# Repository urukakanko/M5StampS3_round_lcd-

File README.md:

# M5StampS3ラウンド液晶モジュール

写真左：M5StampS3実装済　　　　写真右：M5StampS3未実装

M5StampS3を使用して1.28インチ240ｘ240ドットの円形液晶を駆動する基板モジュールです。

円形液晶の裏にM5StampS3を配置することで、とても小さくスリムな形状になりました。

円形液晶にはGC9A01というコントローラーが使用されていますが、対応したグラフィックライブラリが数種類公開されています。

本モジュールは「グラフィックライブラリの使い方を理解して液晶モジュールを駆動出来る人」をターゲットにしております。

# 2026年10月販売分よりM5StampS3実装品はM5StampS3Aを実装しています

# 2023年5月5日までにM5StampS3実装品を購入された方へのお詫び

裏面のMacAddressがプリントされたラベルと実際のMacAddressが異なっている可能性があります。

MacAddress情報が必要な場合は以下サンプルソースで画面表示する様にしましたのでこちらで確認をお願いします。

大変ご迷惑をお掛けしてしまい申し訳ございません。

https://github.com/urukakanko/M5StampS3_round_lcd-/tree/main/M5stampS3_ClockSample

# <span style="color: red;">注意！！（必ずお読み下さい）</span>

本品は基本的な電子回路の仕組みを理解した方を対象とした、電子部品がむき出しの半完成キットです。
電子部品は電源電圧や極性を間違えたり、部品を破損させたり部品端子をショートさせた場合、発熱・発煙・発火に至る場合もあります。
間違った使い方をすると危険である事を理解された方のみご使用ください。
趣味の電子工作向けに製作しておりますので、製品への組込みや日常生活へ組込んでのご使用はお控え下さい。

# 形状および回路図

以下に外形イメージを示します

以下に回路図を示します　現在最新は基板Ver1.0です

試作版のVer0.1の図面は以下に保存しています

https://github.com/urukakanko/M5StampS3_round_lcd-/tree/main/ver0.1

# ピンアサイン

M5Stamp とLCDの制御信号とのピン接続は以下となります。

- SCLK:G1

- DATA-IN:G15

- DC:G7

- CS:G5

- RST:G13

- バックライト:G9　バックライトLEDのPIN設定は必ず行ってください。ハイインピーダンスとなった場合バックライトが不安定になります。

TFカードスロットのPIN接続は以下となります。（SCLKおよびMOSIは液晶と共通です）

- TF-MISO:G43
- TF-CS:44

また、以下の未使用PINはパットで引き出せるようにしました。I2C接続を想定しG39とG40にはプルアップをしています。

- G2,G3,G4,G6,G8,G10,G11,G12,G14,G39,G0,G40,EN,G41,G42,G46

注意：リード線をハンダ付けするパットとして使用します　コネクタやピンヘッダは挿せません。

# 使用するツールやライブラリ

M5StampS3の情報については、以下サイトを参考下さい。

https://docs.m5stack.com/en/core/StampS3

グラフィックライブラリについてはlovyanさまのLovyanGFXにて動作確認をしています。

https://github.com/lovyan03/LovyanGFX

他、GC9A01に対応したライブラリが使用可能と考えています。

# サンプルプログラム

LovyanGFXのClockSampleです

https://github.com/urukakanko/M5StampS3_round_lcd-/tree/main/M5stampS3_ClockSample

# LCD表示動画

BMPデータを液晶に表示しています

[https://youtu.be/gN_2BcIaoQU](https://youtu.be/WFxbUNVwUNw)

未実装版のチェックをしている動画です

https://youtu.be/jMZeYKtBkwM

# そーたメイ氏の「つくるっち」に対応して頂きました

以下はアニメーションデモです

https://sohta02.sakura.ne.jp/tukurutch/#000000531

# 使用例

準備中

# スイッチサイエンスマーケットプレイスで販売しています

M5StampS3実装品

https://www.switch-science.com/products/8971

M5StampS3未実装品

https://www.switch-science.com/products/8851

# 製作者

ウルカテクノロジー
Hiroyuki Sunagawa

https://www.facebook.com/URUKA-Technologies-105478404379918

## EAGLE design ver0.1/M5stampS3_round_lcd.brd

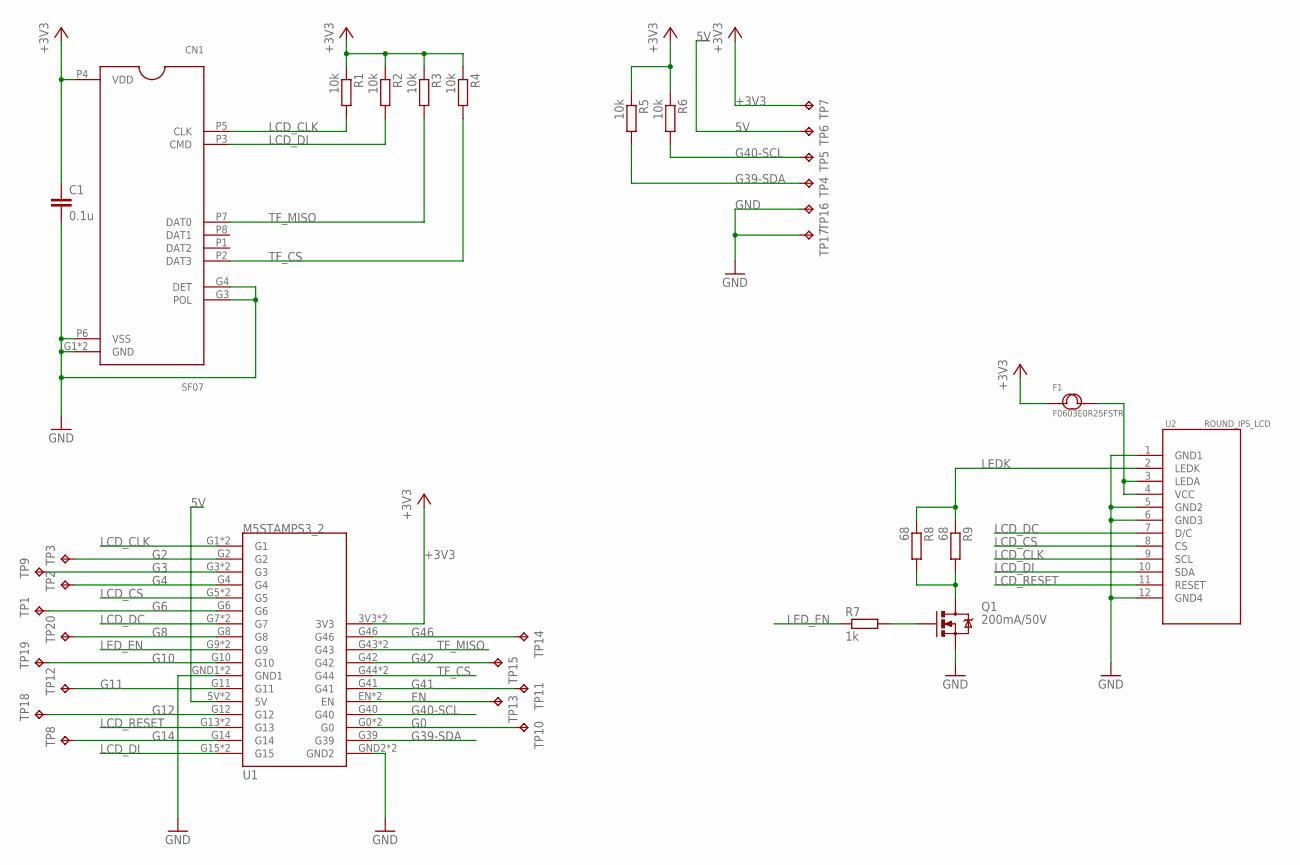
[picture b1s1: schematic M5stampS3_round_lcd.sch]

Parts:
C1: 0.1u; C0603
CN1: SF07; POS-8
F1: F0603E0R25FSTR; C0603
Q1: 200mA/50V; SOT23-3
R1, R2, R3, R4, R5, R6: 10k; R0603
R7: 1k; R0603
R8, R9: 68; R0603
TP1, TP2, TP3, TP4, TP5, TP6, TP7, TP8, TP9, TP10, TP11, TP12, TP13, TP14, TP15, TP16, TP17, TP18, TP19, TP20: TPTP18R; TP18R
U1: M5STAMPS3_2
U2: ROUND_IPS_LCD

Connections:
5V: TP6.TP, U1.5V, U1.5V_ (5V)
+3V3: C1.1, CN1.P4 (VDD), F1.1, R1.1, R2.1, R3.1, R4.1, R5.1, R6.1, TP7.TP, U1.3V3, U1.3V3_ (3V3)
EN: TP13.TP, U1.EN, U1.EN_ (EN)
G0: TP10.TP, U1.G0, U1.G0_ (G0)
G2: TP3.TP, U1.G2
G3: TP9.TP, U1.G3, U1.G3_ (G3)
G4: TP2.TP, U1.G4
G6: TP1.TP, U1.G6
G8: TP20.TP, U1.G8
G10: TP19.TP, U1.G10
G11: TP12.TP, U1.G11
G12: TP18.TP, U1.G12
G14: TP8.TP, U1.G14
G39-SDA: R5.2, TP4.TP, U1.G39
G40-SCL: R6.2, TP5.TP, U1.G40
G41: TP11.TP, U1.G41
G42: TP15.TP, U1.G42
G46: TP14.TP, U1.G46
GND: C1.2, CN1.G1 (GND), CN1.G2 (GND), CN1.G3 (POL), CN1.G4 (DET), CN1.P6 (VSS), Q1.2 (S), TP16.TP, TP17.TP, U1.GND1, U1.GND1_ (GND1), U1.GND2, U1.GND2_ (GND2), U2.1 (GND1), U2.5 (GND2), U2.6 (GND3), U2.12 (GND4)
LCD_CLK: CN1.P5 (CLK), R1.2, U1.G1, U1.G1_ (G1), U2.9 (SCL)
LCD_CS: U1.G5, U1.G5_ (G5), U2.8 (CS)
LCD_DC: U1.G7, U1.G7_ (G7), U2.7 (D/C)
LCD_DI: CN1.P3 (CMD), R2.2, U1.G15, U1.G15_ (G15), U2.10 (SDA)
LCD_RESET: U1.G13, U1.G13_ (G13), U2.11 (RESET)
LEDK: R8.1, R9.1, U2.2 (LEDK)
LED_EN: R7.1, U1.G9, U1.G9_ (G9)
unnamed: Q1.3 (D), R8.2, R9.2
unnamed: Q1.1 (G), R7.2
unnamed: F1.2, U2.3 (LEDA), U2.4 (VCC)
TF_CS: CN1.P2 (DAT3), R4.2, U1.G44, U1.G44_ (G44)
TF_MISO: CN1.P7 (DAT0), R3.2, U1.G43, U1.G43_ (G43)

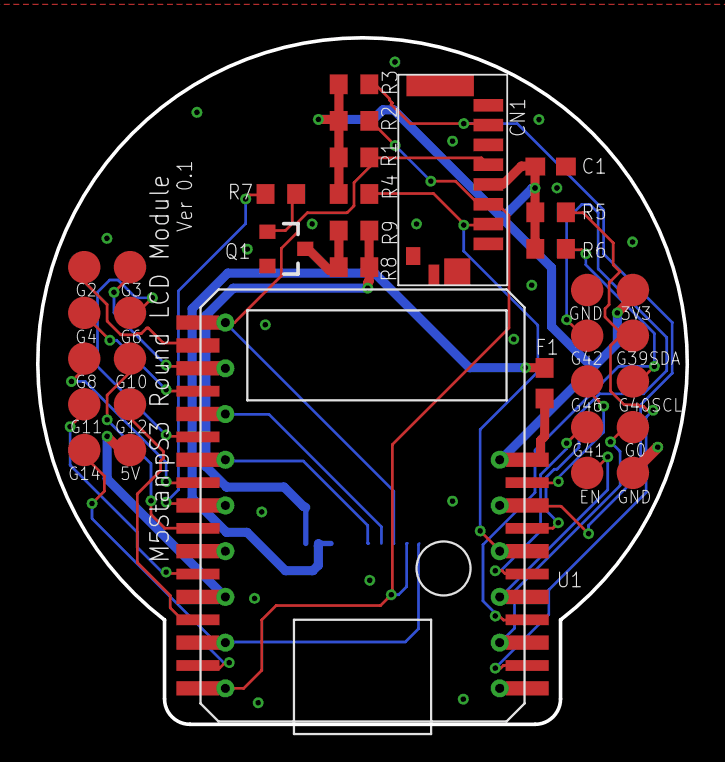
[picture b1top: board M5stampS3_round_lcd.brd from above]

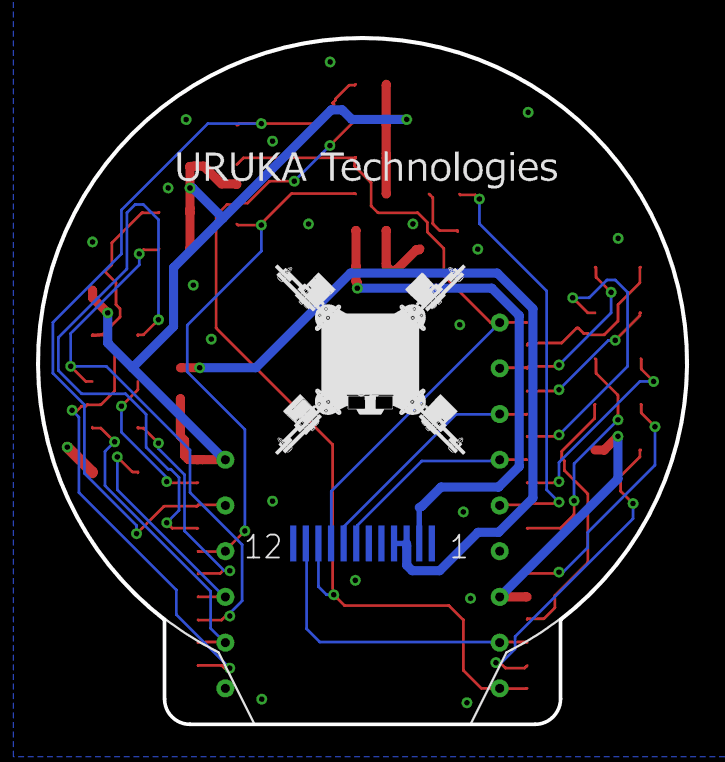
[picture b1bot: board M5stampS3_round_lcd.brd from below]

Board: 2 copper layers, 36.1 x 38.1 mm, 37 parts (2 on the bottom side), 31 nets.

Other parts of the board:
U$1: QC02
U$2: URUKA

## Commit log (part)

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2023-05-08 MacAddress表示を追加
2024-03-10 Gerber file

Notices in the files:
parts and their libraries:
SparkFun-Aesthetics: Licensing: Creative Commons ShareAlike 4.0 International - https://creativecommons.org/licenses/by-sa/4.0
